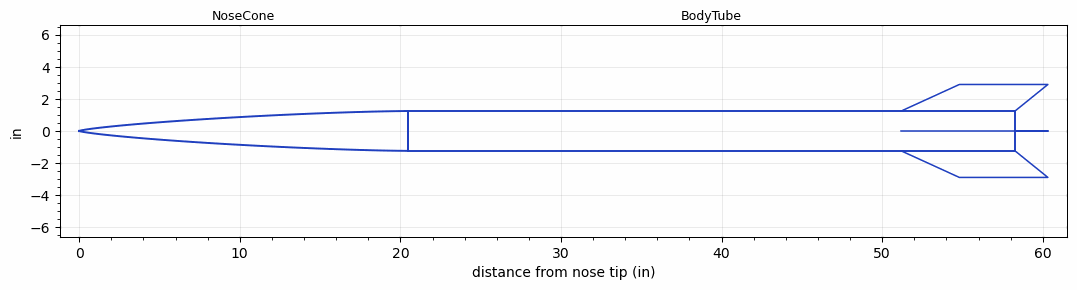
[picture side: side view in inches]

<RASAeroDocument>
 <FileVersion>2</FileVersion>
 <RocketDesign>
  <NoseCone>
   <Length>20.4724</Length>
   <Diameter>2.4803</Diameter>
   <Shape>Von Karman Ogive</Shape>
   <Location>0</Location>
  </NoseCone>
  <BodyTube>
   <Length>37.7952</Length>
   <Diameter>2.4803</Diameter>
   <Location>20.4724</Location>
   <Fin>
    <Count>4</Count>
    <Chord>7.0866</Chord>
    <Span>1.6535</Span>
    <SweepDistance>3.622</SweepDistance>
    <TipChord>5.5118</TipChord>
    <Thickness>0.1181</Thickness>
    <Location>7.0866</Location>
    <AirfoilSection>Square</AirfoilSection>
   </Fin>
  </BodyTube>
  <Surface>Rough Camouflage Paint</Surface>
  <CD>0</CD>
  <ModifiedBarrowman>False</ModifiedBarrowman>
  <Turbulence>False</Turbulence>
  <UseBooster1>False</UseBooster1>
  <UseBooster2>False</UseBooster2>
 </RocketDesign>
 <LaunchSite>
  <Altitude>0</Altitude>
  <Pressure>29.9214</Pressure>
  <RodAngle>0</RodAngle>
  <RodLength>3.2808</RodLength>
  <Temperature>59</Temperature>
  <WindSpeed>4.4739</WindSpeed>
 </LaunchSite>
 <Recovery>
  <Altitude1>0</Altitude1>
  <Altitude2>0</Altitude2>
  <DeviceType1>None</DeviceType1>
  <DeviceType2>None</DeviceType2>
  <Event1>False</Event1>
  <Event2>False</Event2>
  <Size1>0</Size1>
  <Size2>0</Size2>
  <EventType1>None</EventType1>
  <EventType2>None</EventType2>
  <CD1>0</CD1>
  <CD2>0</CD2>
 </Recovery>
 <SimulationList>
  <Simulation>
   <SustainerLaunchWt>10.6724</SustainerLaunchWt>
   <SustainerCG>38.4101</SustainerCG>
   <SustainerIgnitionDelay>0</SustainerIgnitionDelay>
   <Booster1SeparationDelay>0</Booster1SeparationDelay>
   <Booster1IgnitionDelay>0</Booster1IgnitionDelay>
   <IncludeBooster1>False</IncludeBooster1>
   <Booster2Delay>0</Booster2Delay>
   <IncludeBooster2>False</IncludeBooster2>
  </Simulation>
 </SimulationList>
</RASAeroDocument>
